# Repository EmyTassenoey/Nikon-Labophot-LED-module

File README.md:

# Nikon-Labophot-LED-module
LED module for Nikon Labophot (UV and Visible spectrum)

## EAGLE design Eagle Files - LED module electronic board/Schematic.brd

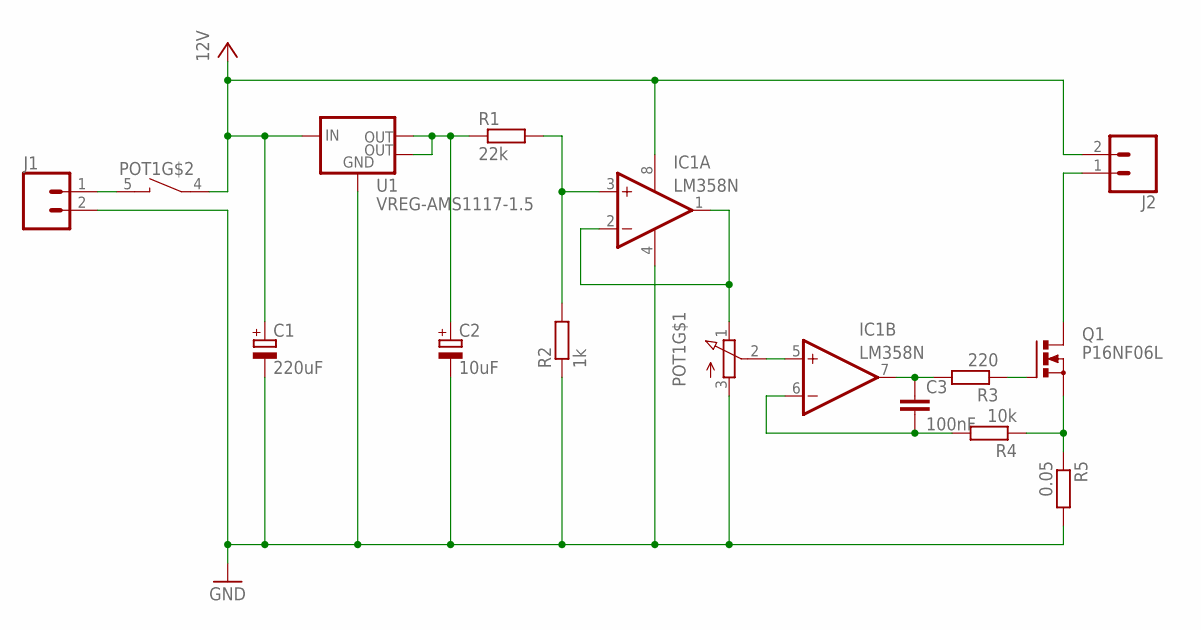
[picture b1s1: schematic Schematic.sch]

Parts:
C1: 220uF; PANASONIC_F
C2: 10uF; PANASONIC_B
C3: 100nF; C025-025X050
IC1: LM358N; DIL08
J1, J2: SCREW-TERM; 1X02_NO_SILK
POT1: POT-SWITCH; POT-SWITCH-PTH
Q1: P16NF06L; TO220BV
R1: 22k; R1206
R2: 1k; R1206
R3: 220; R1206
R4: 10k; R1206
R5: 0.05; R2512
U1: VREG-AMS1117-1.5; SOT230P700X180-4

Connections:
GND: C1.-, C2.-, IC1.4 (V-), J1.2 (1), POT1.3, R2.1, R5.2, U1.1 (GND)
unnamed: J1.1 (2), POT1.5
unnamed: IC1.3 (+IN), R1.2, R2.2
unnamed: C2.+, R1.1, U1.2 (OUT), U1.4 (OUT)
unnamed: IC1.1 (OUT), IC1.2 (-IN), POT1.1
unnamed: J2.1 (2), Q1.D
unnamed: C3.1, IC1.7 (OUT), R3.2
unnamed: Q1.G, R3.1
unnamed: C3.2, IC1.6 (-IN), R4.2
unnamed: Q1.S, R4.1, R5.1
unnamed: IC1.5 (+IN), POT1.2
VCC: C1.+, IC1.8 (V+), J2.2 (1), POT1.4, U1.3 (IN)

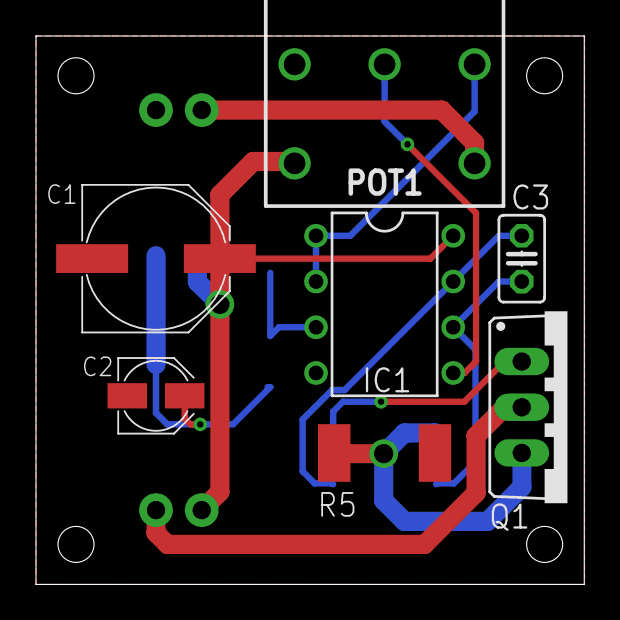
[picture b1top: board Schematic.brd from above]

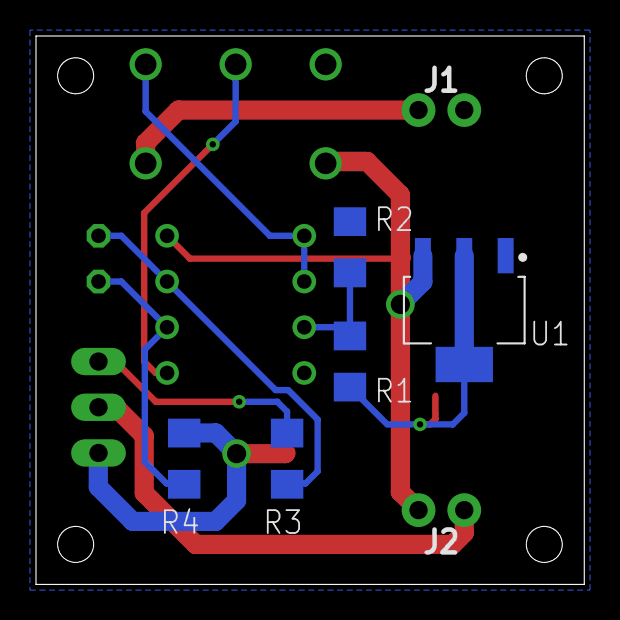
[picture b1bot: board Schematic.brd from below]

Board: 2 copper layers, 30.5 x 30.5 mm, 14 parts (7 on the bottom side), 12 nets.

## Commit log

2019-03-03 Assembly pictures
2019-03-03 Versions updated
2019-03-19 Major changes!
    Major changes! Do not use older version, pins swapped in V-regulator.
2019-03-19 Minor changes in footprints
